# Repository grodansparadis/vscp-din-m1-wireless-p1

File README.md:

# vscp-din-m1-wireless-p1
Application board for VSCP DIN M1 based module that read P1 metering data

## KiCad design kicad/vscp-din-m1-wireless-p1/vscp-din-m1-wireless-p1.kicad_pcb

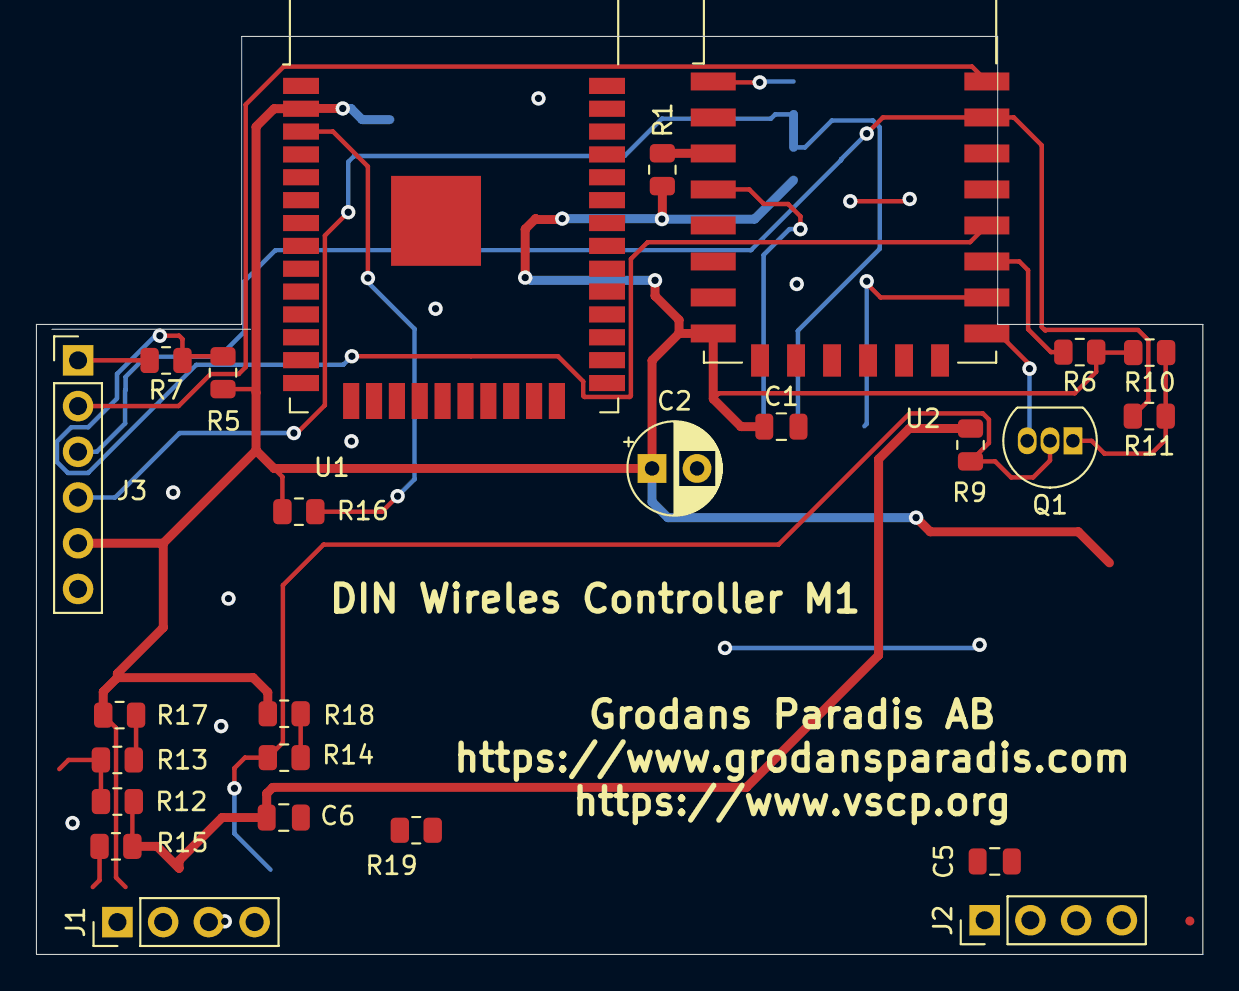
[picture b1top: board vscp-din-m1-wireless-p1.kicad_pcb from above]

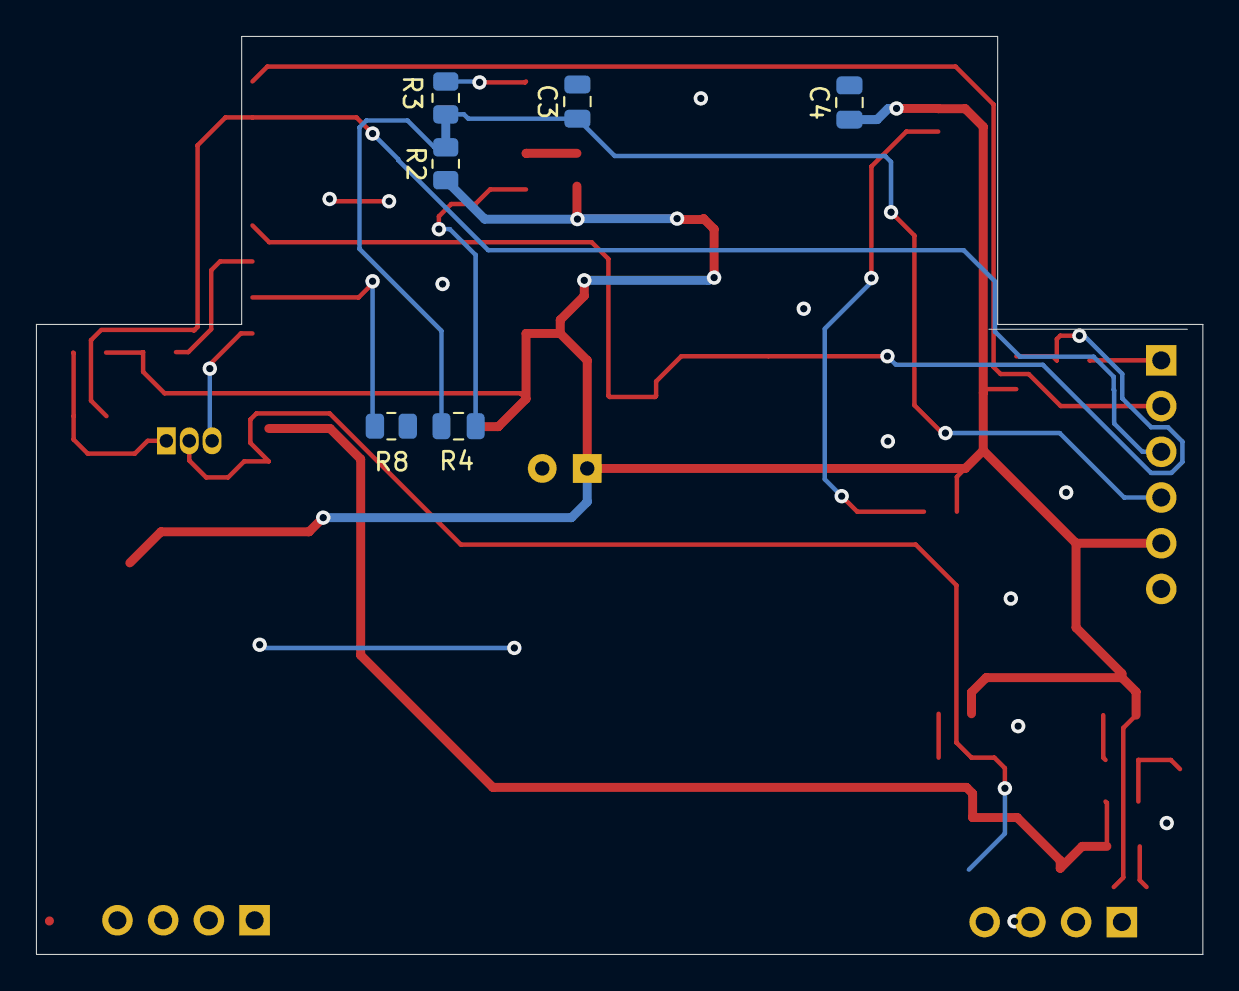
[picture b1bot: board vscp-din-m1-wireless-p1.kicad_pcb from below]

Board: 2 copper layers, 64.8 x 51.0 mm, 31 parts (6 on the bottom side), 20 nets.

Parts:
C1, C3, C4, C5, C6: 100nF; C_0805_2012Metric
C2: 1000uF; CP_Radial_D5.0mm_P2.50mm
J1: Conn_01x04_Left; PinHeader_1x04_P2.54mm_Vertical
J2: Conn_01x04_Right; PinHeader_1x04_P2.54mm_Vertical
J3: Conn_01x06; PinHeader_1x06_P2.54mm_Vertical
Q1: BC547; TO-92_Inline
R1, R2, R5, R6, R8, R10, R16, R19: 10K; R_0805_2012Metric
R3, R7: 470; R_0805_2012Metric
R4: 470; C_0805_2012Metric
R9, R17, R18: 4k7; R_0805_2012Metric
R11: 0; R_0805_2012Metric
R12, R13, R14, R15: 0R; R_0805_2012Metric
U1: ESP32-WROOM-32D; ESP32-WROOM-32
U2: ESP-12E

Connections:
/FLASH: J3.1, R7.2
/RESET: C3.1, J3.4, R2.2, R3.2, R4.1
/RXD: J3.3, R11.2, U2.21
/TXD: J3.2, U2.22
GND: C1.2, C2.2, C3.2, C4.2, C5.2, C6.2, J1.4, J2.1, J3.6, Q1.3, R8.1, U1.1, U1.15, U1.38, U1.39, U2.15
unnamed: J1.2, R12.1, R13.1
unnamed: J1.3, Q1.2, R9.1, R14.1
unnamed: Q1.1, R10.1, R11.1
unnamed: R1.2, U2.3
unnamed: R3.1, U2.1
unnamed: R4.2, U2.4
unnamed: R5.2, R7.1, U2.18
unnamed: R6.2, U2.17
unnamed: R8.2, U2.16
unnamed: R13.2, R17.1
unnamed: R14.2, R18.1
unnamed: R15.1, R19.1
unnamed: R16.2, U1.3
VCC: C1.1, C2.1, C4.1, C5.1, J2.4, J3.5, R1.1, R2.1, R5.1, R6.1, R10.2, R16.1, R17.2, R18.2, R19.2, U1.2, U2.8
VDD: C6.1, J1.1, R9.2, R12.2, R15.2

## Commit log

2021-05-20 First version
2021-05-21 Generated gerbers
2021-05-24 Added vanilla DIN board
2021-05-25 Fixed board to board connector
2021-05-25 Fixed power
2022-06-15 Updated design files
